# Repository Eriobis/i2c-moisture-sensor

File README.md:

# i2c-moisture-sensor
BLE Moisture Sensor
Based on Miceuz's work 
 - I2C based soil moisture sensor. A continuation of the [Chirp - plant watering alarm](https://github.com/Miceuz/PlantWateringAlarm) project. There is also an [RS485](https://github.com/Miceuz/rs485-moist-sensor) and an [analog](https://github.com/Miceuz/soil-moisture-sensor-analog) version available.

## BLE advertisement packet
Advertisement data description 

- 2 Bytes - Specific manufacturer data : 0xFFFF ( no manufacturer )
- 4 bytes (float) -> Vcc ( Vbatt )
- 4 bytes (float) -> Sense value
- 4 bytes (float) -> SPARE1
- 4 bytes (float) -> SPARE2

Advertise data example :
``` c
uint8_t adv_data[] = {
    /* Advertising data: Flags AD Type */
    0x02, 
    AD_TYPE_FLAGS,
    FLAG_BIT_LE_GENERAL_DISCOVERABLE_MODE | FLAG_BIT_BR_EDR_NOT_SUPPORTED, 
    0x06,                                 // Len
    AD_TYPE_SHORTENED_LOCAL_NAME,         // Local name
    'S', 'B', 'M', 'S', '1',
    /* Advertising data: manufacturer specific data */
    0x13,                                 // Len ( 19 )
    AD_TYPE_MANUFACTURER_SPECIFIC_DATA,   // manufacturer type
    0xFF, 0xFF,                           // Company identifier code (Default is 0x0030 -
                                          // STMicroelectronics: To be customized for specific identifier)
                                          // FFFF = No identifier
    'D', 'A', 'T', 'A',                   // Vcc in float
    'D', 'A', 'T', 'A',                   // Sense value
    'D', 'A', 'T', 'A',
    'D', 'A', 'T', 'A',
};
```

## Debug adaptor

A ST-LinkV2 can be used to program the chip.

The connector is based on the J-Link 9 pins pinout. 
https://www.segger.com/products/debug-probes/j-link/accessories/adapters/9-pin-cortex-m-adapter/

## Code

At this moment, this repo is only for the HW design, the code is in another repo.

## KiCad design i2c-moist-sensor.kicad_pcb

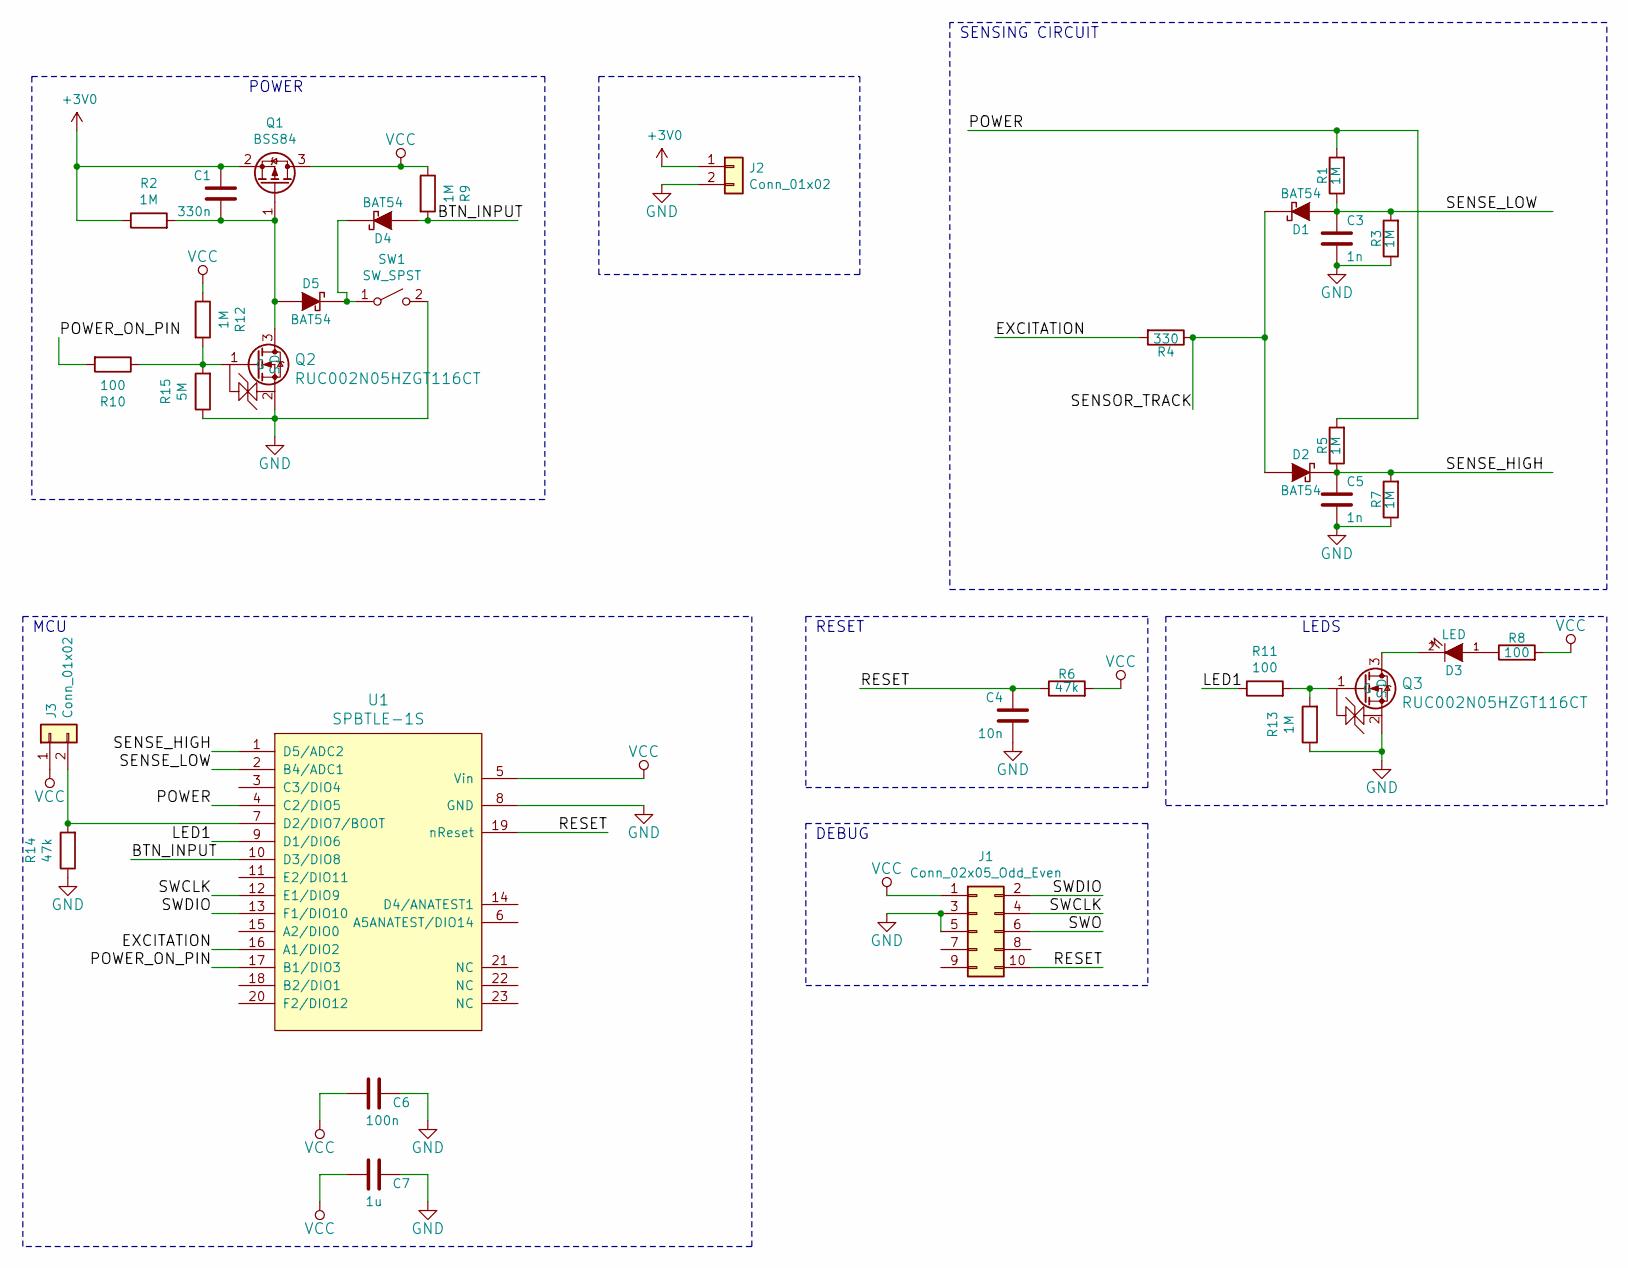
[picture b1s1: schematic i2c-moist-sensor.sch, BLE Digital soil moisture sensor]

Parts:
C1: 330n; C_0603_HandSoldering; PartNo MC0603X105K100CT
C3, C5: 1n; C_0603_HandSoldering; PartNo MC0603B102K500CT
C4: 10n; C_0603_HandSoldering; PartNo MC0603X105K100CT
C6: 100n; C_0603_HandSoldering; PartNo MC0603X105K100CT
C7: 1u; C_0603_HandSoldering; PartNo MC0603X105K100CT
D1, D2, D4, D5: BAT54; D_SOD-523; PartNo BAT54XV2
D3: LED; LED_0603_HandSoldering; PartNo KP-1608SURCK
J1: Conn_02x05_Odd_Even; 50mils_JTAG
J2, J3: Conn_01x02; Pin_Header_Straight_1x02_Pitch2.54mm
Q1: BSS84; SOT-23_Handsoldering
Q2, Q3: RUC002N05HZGT116CT; SOT-23_Handsoldering
R1, R3, R5, R7: 1M; R_0603_HandSoldering; PartNo MCWR06X1004FTL
R2, R9, R12, R13: 1M; R_0603_HandSoldering
R4: 330; R_0603_HandSoldering; PartNo MCWR06X3300FTL
R6: 47k; R_0603_HandSoldering; PartNo ERJ3RBD1002V
R8: 100; R_0603_HandSoldering; PartNo MCWR06X3300FTL
R10, R11: 100; R_0603_HandSoldering
R14: 47k; R_0603_HandSoldering
R15: 5M; R_0603_HandSoldering
SW1: SW_SPST; TL3305AF160QG
U1: SPBTLE-1S; SPBTLE-1s

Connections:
+3V0: C1.1, J2.1, Q1.2 (S), R2.1
/BTN_INPUT: D4.1 (A), R9.2, U1.10 (D3/DIO8)
/EXCITATION: R4.2, U1.16 (A1/DIO2)
/LED1: R11.1, U1.9 (D1/DIO6)
/POWER: R1.2, R5.2, U1.4 (C2/DIO5)
/POWER_ON_PIN: R10.2, U1.17 (B1/DIO3)
/RESET: C4.1, J1.10, R6.1, U1.19 (nReset)
/SENSE_HIGH: C5.1, D2.2 (K), R5.1, R7.2, U1.1 (D5/ADC2)
/SENSE_LOW: C3.1, D1.1 (A), R1.1, R3.2, U1.2 (B4/ADC1)
/SENSOR_TRACK: D1.2 (K), D2.1 (A), R4.1
/SWCLK: J1.4, U1.12 (E1/DIO9)
/SWDIO: J1.2, U1.13 (F1/DIO10)
GND: C3.2, C4.2, C5.2, C6.1, C7.1, J1.3, J1.5, J2.2, Q2.2 (S), Q3.2 (S), R3.1, R7.1, R13.1, R14.1, R15.1, SW1.2 (B), U1.8 (GND)
unnamed: C1.2, D5.1 (A), Q1.1 (G), Q2.3 (D), R2.2
unnamed: D3.1 (A), R8.1
unnamed: D3.2 (K), Q3.3 (D)
unnamed: D4.2 (K), D5.2 (K), SW1.1 (A)
unnamed: J3.2, R14.2, U1.7 (D2/DIO7/BOOT)
unnamed: Q2.1 (G), R10.1, R12.2, R15.2
unnamed: Q3.1 (G), R11.2, R13.2
VCC: C6.2, C7.2, J1.1, J3.1, Q1.3 (D), R6.2, R8.2, R9.1, R12.1, U1.5 (Vin)

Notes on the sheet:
DEBUG
LEDS
RESET
POWER
SENSING CIRCUIT
MCU

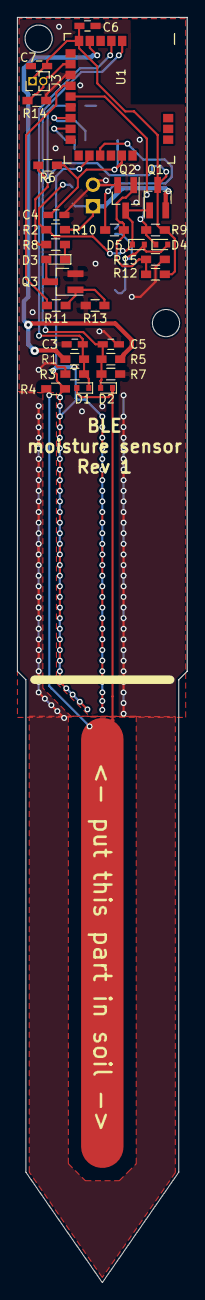
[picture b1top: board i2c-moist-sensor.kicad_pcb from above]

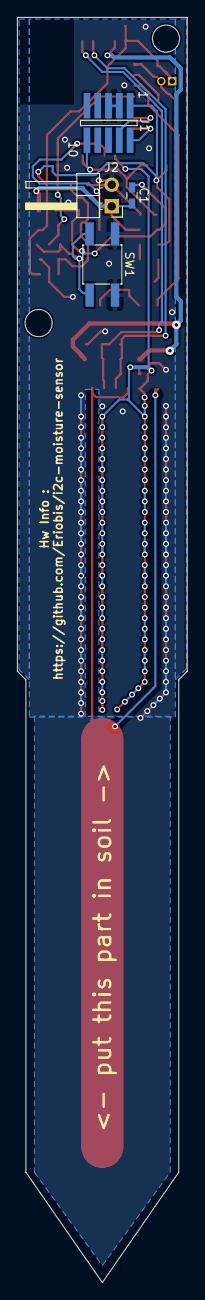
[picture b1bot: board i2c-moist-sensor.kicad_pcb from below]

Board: 2 copper layers, 20.0 x 149.0 mm, 34 parts (4 on the bottom side), 21 nets.

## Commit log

2019-09-14 SPBTLE version 1.0 - HW
    Only hardware changes
2019-10-09 Add gerber BLE 1.0
2019-10-09 test
2019-10-27 Updated to Rev1
    - Naming from 1.0 to Rev version number
    - Added pull up for vcc latch
    - Added button input
    - Removed led2
    - Added BOOT pin jumper and pullup
